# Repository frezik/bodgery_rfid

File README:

RFID system for The Bodgery <http://thebodgery.org>

# INSTALL OF SERVER

Installation on a Ubuntu/Debian based Linux distribution:

* Clone the respository
* Install cpanminus and postgresql: `sudo apt-get install cpanminus postgres-all`
* Install dependencies: `sudo cpanm --installdeps`
* Install Starman: `sudo cpanm Starman`
* Create a user for postgresql
* Create a database in postgresql called "bodgery_rfid", with full access to 
  the user created above
* Create the tables in the database: `psql --file postgresql.sql bodgery_rfid`
* Run the server with starman: `starman --listen :3000 app.pl`

The server should now be accessible on localhost at port 3000.

# PINS

Pins Used on the Rpi Model B+.  Numbered by physical header, not GPIO number.

Pin     Function
---     --------
1       Open/closed door pushbutton switch power (3.3V)
7       LED open signal (GPIO4)
9       LED open signal ground (GND)
11      Open/closed door pushbutton switch (GPIO17)
13      Relay enable pin (GPIO27)
15      Lock Relay (GPIO22)
16      Open/closed shop toggle switch (GPIO23)
17      Open/closed shop toggle switch power (3V3)
22      Unlock Switch (GPIO25)
25      Relay ground (GND)

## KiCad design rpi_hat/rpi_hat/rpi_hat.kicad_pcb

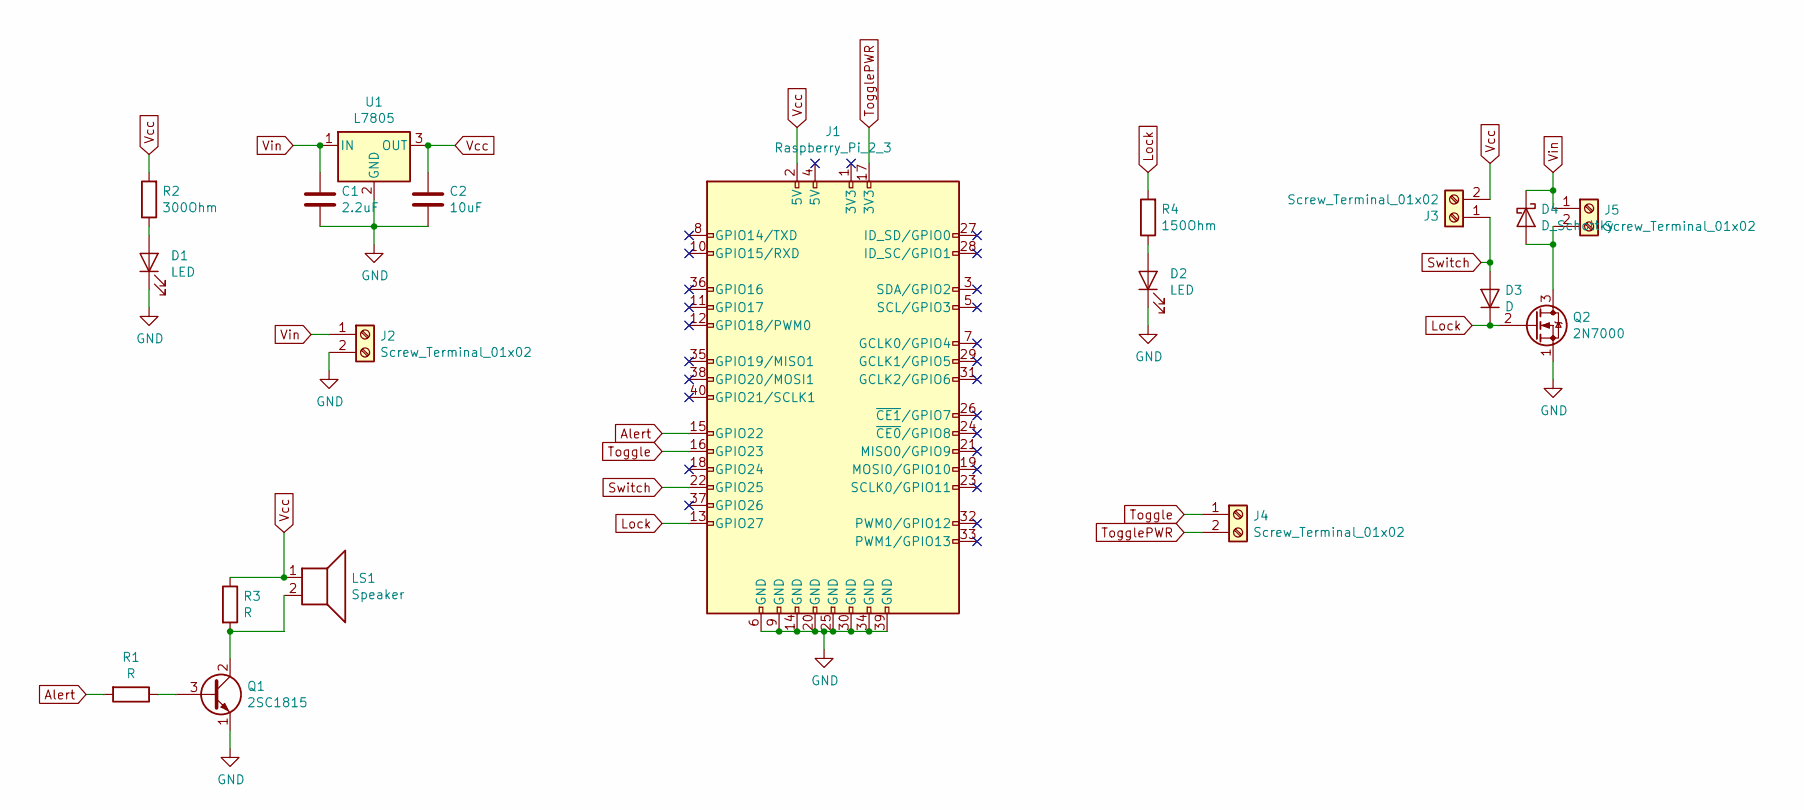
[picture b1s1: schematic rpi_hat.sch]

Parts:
C1: 2.2uF; C_0402; Digikey # 490-12532-1-ND
C2: 10uF; C_0805; Digikey # 1276-6456-1-ND
D1: LED; LED_0603; Digikey # SML-D12U1WT86CT-ND
D2: LED; LED_0603; Digikey # 160-1478-1-ND
D3: D; SOD-123; Digikey # 1N4148WTPMSCT-ND
D4: D_Schottky; SOD-123; Digikey # MBR0540T3GOSCT-ND
J1: Raspberry_Pi_2_3; Pin_Header_Straight_2x20; Digikey # 1528-1785-ND
J2, J3, J4, J5: Screw_Terminal_01x02; TerminalBlock_Pheonix_MKDS1.5-2pol; Digikey # 277-1667-ND
LS1: Speaker; PS1240P02BT; Digikey # 445-2525-1-ND
Q1: 2SC1815; TO-92_Inline_Wide; Digikey # KSC1815YTACT-ND
Q2: 2N7000; TO-220_Neutral123_Horizontal; Digikey # 497-2779-5-ND
R1, R3: R; R_0805; Digikey # RNCP0805FTD1K00CT-ND
R2: 300Ohm; R_2512; Digikey # RMCF2512JT300RCT-ND
R4: 150Ohm; R_0603; Digikey # P150DBCT-ND
U1: L7805; Pin_Header_Angled_1x03; Digikey # 1589-1465-ND

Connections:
Alert: J1.15 (GPIO22), R1.2
GND: C1.2, C2.2, D1.1 (K), D2.1 (K), J1.6 (GND), J1.9 (GND), J1.14 (GND), J1.20 (GND), J1.25 (GND), J1.30 (GND), J1.34 (GND), J1.39 (GND), J2.2, Q1.1 (E), Q2.1 (S), U1.2 (GND)
Lock: D3.1 (K), J1.13 (GPIO27), Q2.2 (G), R4.2
unnamed: D1.2 (A), R2.1
unnamed: D2.2 (A), R4.1
unnamed: D4.2 (A), J5.2, Q2.3 (D)
unnamed: LS1.2, Q1.2 (C), R3.2
unnamed: Q1.3 (B), R1.1
Switch: D3.2 (A), J1.22 (GPIO25), J3.1
Toggle: J1.16 (GPIO23), J4.1
TogglePWR: J1.17 (3V3), J4.2
Vcc: C2.1, J1.2 (5V), J3.2, LS1.1, R2.2, R3.1, U1.3 (OUT)
Vin: C1.1, D4.1 (K), J2.1, J5.1, U1.1 (IN)

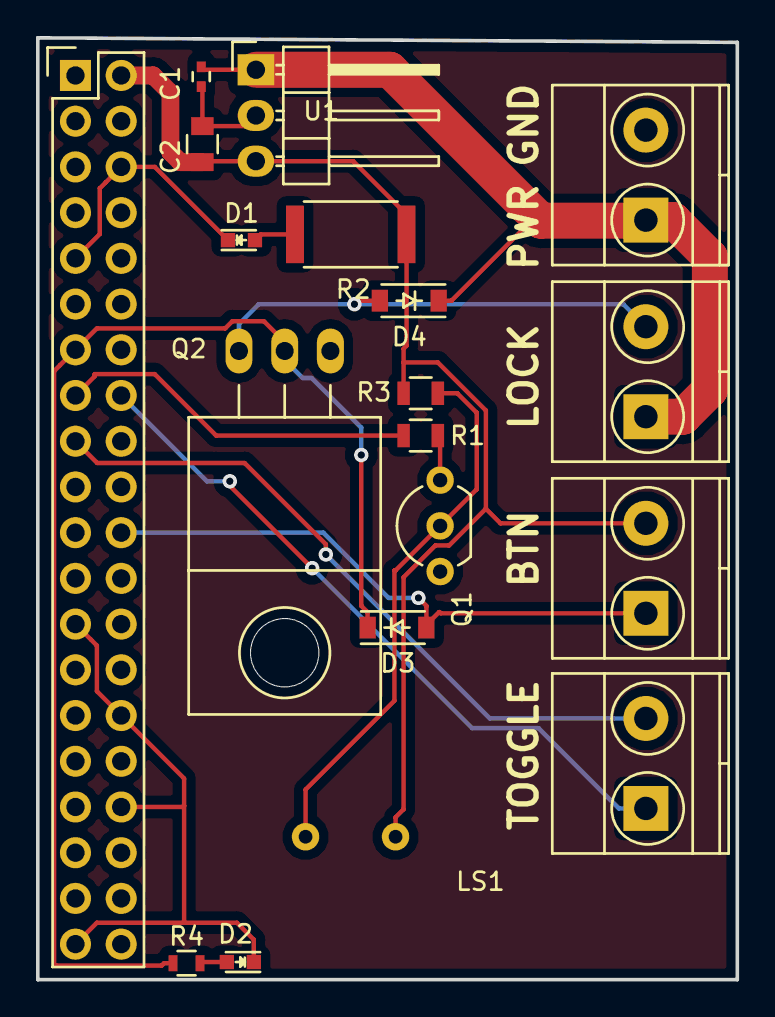
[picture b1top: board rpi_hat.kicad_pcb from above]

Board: 2 copper layers, 38.9 x 52.3 mm, 19 parts (0 on the bottom side), 13 nets.

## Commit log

2014-12-22 Initial import
2014-12-22 Update numbers for RPi-based solution
2014-12-22 Implement REST interface
2014-12-23 Start on client lib
2014-12-23 PostgreSQL table definitions
2014-12-23 Log entry times and failures
2014-12-29 * Add power adaptor circuit * Page for adding new RFID tag * Add calls for searching tags and entry log * Flesh out index definitions * Flesh out client action breakdown
2014-12-29 Flesh out PostgreSQL tables and adding RFID calls
2014-12-29 Page for viewing member list. When searching name, do it in a case-insensitive manner, with a prefix search
2014-12-29 Activate/deactivate buttons work
2014-12-29 Remove unnecessary SQL statements
2014-12-29 Search entry log. Handle the Full Name field on entries that don't match up.
2014-12-29 Control door lock and piezo
2014-12-29 Tweak good and bad tones
2014-12-29 Clear current TODO list
2014-12-31 Add README
2014-12-31 Add BSD 2-clause license
2014-12-31 Remove budget doc
2015-01-02 Add page for testing RFID tag
2015-01-02 Flesh out Test Tag page
2015-01-02 Add --test parameter. Don't die when we get an error from the server.
2015-01-13 Add dumping of all active tags via Sereal
2015-01-13 Script to fetch a fallback DB. Modify client to check it.
2015-01-13 Fix fetching of fallback DB. Log output fix for various situations.
2015-01-15 Order entry log the right way
2015-01-15 Put entry log the correct way, for real this time
2015-01-15 Revert "Put entry log the correct way, for real this time"
    This reverts commit 742e621fd498be9bd73a224607db29793e825f53.
2015-01-15 Refresh after deactivating/activating a user
2015-01-24 Use software write for piezo tones
2015-01-24 Use Zelda notes for entry
2015-01-24 Final version for hack and tell night
2015-01-25 Cleanup compile errors. Get TODO list going. Document which pins go to what.
2015-01-25 Request to server is now async
2015-01-25 Parameter for fallback DB path
2015-01-27 Correct syntax errors and missing modules caught during testing
2015-01-27 Correct pins for LCD. Change others to be compatible with the Rpi Model B rather than B+
2015-01-27 Check off a bunch of items
2015-03-14 Fix unlock LED and LCD
2015-03-23 Move LCD power off a GPIO pin
2015-06-12 Add GPIO info to pin description
2015-06-12 Add piezo pin
2015-06-13 Set pullups on lock pins. Optionally disable LCD screen.
2015-06-24 Change relay to switch
2015-06-24 Remove debugging settings
2015-06-28 Qualifying exam for Star Fleet Corps of Engineers: fix something by reversing the polarity
2015-07-02 Correct shebang for Rpi. Script to manually open door
2015-08-13 Hold door open for 10 seconds when open button pushed
2015-09-01 Implement shop open flag
2015-09-01 Implement script for fetching pic when shop is open. Define a client pin for shop open switch.
2015-10-07 Fix chmod
2015-10-08 App's caching of door state uses CHI backend. Clear away LCD, piezo, and picture taking code in client. Also, hold door open if a tag is scanned after pushing the exit button.
2015-10-08 Debug holding door open with a tag scan
2015-10-08 Remove debug timing
2015-10-19 Flesh out script for taking picture during open shop
2015-11-14 Add open switch code
2015-11-14 Will now post to open shop URL
2015-11-14 Only do a one-time check, rather than infinate loop
2015-11-14 Update open/closed shop switch
2016-03-12 Search liability forms
2016-03-12 Correct link to liability search
2016-03-12 Correct passing of search parameters
2016-03-12 Don't start by searching forms
2016-06-11 Always send shop pic on every execution
2016-06-11 Allow extra args to raspistill
2016-06-16 Dump signup emails
2016-06-16 Fix syntax errors
2016-06-16 Fix JavaScript to show emails and submit IDs
2016-07-02 Add cpanfile to track deps
2016-07-02 Add Mojolicious::Plugin::CHI
2016-07-02 Database stores more extensive member info
2016-07-02 Add mojo handlebars dependency
2016-07-12 App accepts updating of cost buckets
2016-10-11 Get rid of all references to custom SSL cert
2016-10-11 New client that gets rid of all the cruft
2016-11-18 Always open between 6 and 10pm on mondays and fridays
2016-11-18 Don't try to dump emails we don't have
2017-01-21 Add temperature logging
2017-01-21 DB changes for temp monitoring
2017-01-21 Update required module
2017-02-17 Strip out unused code. Allow multiple fallback hosts. Check local DB first.
2017-02-18 Play music when people enter
2017-02-24 Put client pins into the README
2017-02-24 Remove piezo from pins
2017-02-25 Name pin usage a little better
2017-02-25 Remove unnecessary dependency
2017-02-25 Fix position of UserAgent construction
2017-02-25 Fix typo
2017-02-25 Shorten input looping
2017-02-25 Remove music. Set pullup on switch pin
2017-02-26 Systemd startup script
2017-02-26 Debug systemd service file. Pushbutton connected to power.
2017-02-27 Add fixed up systemd startup files
2017-05-15 Updated license terms
2018-02-02 Implement pagination of logs on backend
2018-02-02 Frontend support for pagination
2018-07-20 Revert "Updated license terms"
    This reverts commit 7ccce98b576e5db6dfb0701afa18ce81603e20ae.
2018-08-03 API for opening the doorbot
2018-08-03 Frontend for opening door
2018-08-04 Correct tests for searches and fullname/firstname formatting
2018-12-30 Hold door open by holding button while scanning. Close it again by doing the same.
2019-01-04 When canceling a hold open, don't let new timer activate for the button
2019-02-26 PCB for an RPi hat
2019-02-26 Fix pushbutton switch circuit so it doesn't rely on the Pi working
2019-02-26 Correct digikey part # for piezo transistor
2019-02-27 Add protection diode
2019-03-05 Capture keystrokes to simplify RFID tag test
2019-03-05 Add 'checking' message while we wait for a response
2019-03-22 Return of playing music
2019-06-02 Be sure to short-circuit the check when we successfully hit a key in the cache DB
2019-06-02 Marshall's wiegand -> USB keyboard bridge for Teensy
2019-06-04 Variable padding of zeros. Cleanup code.
2019-07-13 Implement JSON as a fallback DB
2020-08-13 Added Delete Functionality
    Added delete endpoint to api and button to tag list.
2020-08-13 Update view_list.html
    Added column for new delete button
2020-08-13 Update app.pl
    Corrected http response code for delete endpoint
2020-08-20 Start on logging entry locations
2020-08-22 Show location on entry log
2020-08-22 Fix tests. Be sure we can log locations with dots in them.
2020-09-04 Install instructions
2020-09-04 Add dummy entry log location
2021-02-26 Optional dump of JSON, rather than Sereal
